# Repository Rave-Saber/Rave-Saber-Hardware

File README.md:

# RaveSaber - AVR Hardware

This repository contains the circuit diagram, PCB schematics, prototype board
layout, parts list, & setup guide for the RaveSaber electronics.

There is no blade or hilt at the moment, but you can swing the LEDs
around using the PCB or prototype board & a piece of wood.

## Electronics Design

The Rave Saber board includes voltage regulation, utility headers, input
buttons, and an Atmel ATmega168a microchip.

### Connectors

`J1` is where power enters the board from the battery. We use JST connectors
for our battery wiring. The battery power is fed through the power sub-circuit
to get a regulated voltage of 5V.

`J2` is where the Dotstar strips connect to the board. The data & clock signals
come from the microchip while the power connections come from the power
circuit.

`J3` & `J4` are optional connectors that ease programming & development. `J3`
is a FTDI Serial connection that can be used to preview/sample different colors
with our [color testing firmware][color-test]. `J4` is an ISP connector that
allows you to re-program the microchip without having to pull it out of it's
socket.

### Power

The power circuit uses a LM2576TV-5G switching voltage regulator to step down
the battery voltage to 5V. It can pump out a maximum of 3 Amps, which is used
to power the microcontroller & the LEDs.

The circuit design is derived from the voltage regulator's datasheet. `C1` &
`C2` should be low-ESR capacitors rated for at least 16V(with a minimum ESR of
50 milliOhms for `C2`). `C2` can be anywhere from 1000 to 2000 uF. `L1` must be
an inductor rated for at least 3 amps, going slightly over that is encouraged.
`D1` should be rated for 20V.

### Microcontroller

The microcontroller circuit is mostly just connections to the other circuits.

Bypass capacitors are used on the connection to the power circuit. `C3` & `C4`
are optional but `C5`, the 100nF capacitor, should always be included. The
analog reference & power pins are connected to the power supply even though
they are not used - this is recommended in the ATmega datasheet.

### Crystal Oscillator

The oscillator circuit is pretty fluid. You can use a different frequency
crystal(with a maximum of 20Mhz), or leave out the entire circuit and use the
ATmega's 8Mhz internal oscillator instead. If you do modify the circuit, make
sure your microcontroller's fuses are correctly programmed for your desired
clock source and change the definition of the `F_CPU` macro in the firmware's
`Makefile` to your new frequency.

### Button

The main button is `SW1`. It is used to ignite/extinguish the saber & cycle
through the programmed patterns. We've included both a tactile switch for
development and an external connection so you can put your board in a hilt.

The reset button, `SW2`, is optional but ocassionally useful for testing &
development.

## Required Materials

### Equipment

You'll want to have the following equipment/supplies:

* 22AWG Solid Hookup Wire
* AVR Programmer(like the [USBtinyISP][usbtinyisp])
* Wire Strippers
* Flush Cutters
* Soldering Iron & Solder
* PCB Holder(optional)
* Anti-static Bracelet or ESD-safe Tweezers(optional)

If you're only testing this out on a breadboard you can get away with just:

* Breadboard
* Wire & Strippers
* AVR Programmer
* 5V Power Supply

### Components

For the breadboard, you just need a Dotstar strip, an ATmega168a
microcontroller & a tactile button.

For the prototyping board, you will need the following:

| Part | Description | Link |
|---|---|---|
| | 22x27 through-hole prototyping board | [Amazon][protoboard] |
| BAT | 7.4v Li-Ion battery | [TCSS][battery] |
| LED | DotStar Strip, 144/m | [Mouser][led-strip] |
| J1 | 2-pin JST connector | [TCSS][jst-power-connector] |
| J2 | 4-pin, 2.54mm pitch male header | [Amazon][headers] |
| J3 | 6-pin, 2.54mm pitch male header | [Amazon][headers] |
| J4 | 2x3-pin, 2.54mm pitch male header | [Amazon][headers] |
| C1 | 100uF low-ESR electrolytic capacitor | [Mouser][100-cap] |
| C2 | 1000-2000uF low-ESR electrolytic capacitor | [Mouser][1200-cap] |
| C3 | 10uF capacitor | [Amazon(assorted)][elec-cap-kit] |
| C4 | 1uF capacitor | [Amazon(assorted)][elec-cap-kit] |
| C5 | 100nF capacitor | [Amazon(assorted)][cer-cap-kit] |
| C6, C7 | 20pF capacitor | [Mouser][20-cap] |
| D1 | 3A, 20V Schottky Diode | [Mouser][diode] |
| L1 | 47uH, 3A Fixed Inductor | [Mouser][inductor] |
| Y1 | 16Mhz Crystal | [Mouser][crystal] |
| SW1, SW2 | 6mm SPST OFF-(ON) tactile switch | [Mouser][switch] |
| U1 | LM2576TV-5G - 5V, 3A switching voltage regulator | [Mouser][vreg] |
| U2 | 28-pin DIP IC socket | [Amazon][dip-socket] |
| U2 | Atmel ATmega168A-PU - AVR microcontroller | [Mouser][atmega] |

[protoboard]: https://amzn.to/2L2IWVJ
[battery]: http://www.thecustomsabershop.com/74v-Li-ion-2600mAh-18650-Battery-Pack-P699.aspx
[led-strip]: https://www.mouser.com/ProductDetail/485-2242
[jst-power-connector]: https://www.thecustomsabershop.com/JST-Female-connector-24AWG-RedBlack-P964.aspx
[headers]: https://amzn.to/2Mx6HtK
[100-cap]: https://www.mouser.com/ProductDetail/710-870135675003
[1200-cap]: https://www.mouser.com/ProductDetail/667-EEU-FC1A122S
[elec-cap-kit]: https://amzn.to/2wb0Ekk
[cer-cap-kit]: https://amzn.to/2PiyX1K
[20-cap]: https://www.mouser.com/ProductDetail/594-S200K25SL0N63L6R
[diode]: https://www.mouser.com/ProductDetail/863-1N5820G
[inductor]: https://www.mouser.com/ProductDetail/673-PE-53112NL
[crystal]: https://www.mouser.com/ProductDetail/520-HCA1600-20X
[switch]: https://www.mouser.com/ProductDetail/506-FSM4JH
[vreg]: https://www.mouser.com/ProductDetail/863-LM2576TV-5G
[dip-socket]: https://amzn.to/2Mo4dOU
[atmega]: https://www.mouser.com/ProductDetail/556-ATMEGA168A-PU

For the circuit board, you will need SMD components instead:

| Part | Description | Link
|---|---|---|
| | RaveSaber v3.0.0 PCB | [OSHPark][pcb-3.0.0]
| BAT | 7.4v Li-Ion battery | [TCSS][battery] |
| LED | DotStar Strip, 144/m | [Mouser][led-strip] |
| J1 | 2-pin JST connector | [TCSS][jst-power-connector]
| J2 | 4-pin, 2.54mm pitch male header | [Mouser][pcb-4-pin]
| J3 | 6-pin, 2.54mm pitch male header | [Mouser][pcb-6-pin]
| J4 | 2x3-pin, 2.54mm pitch male header | [Mouser][pcb-2-3-pin]
| J5 | 2-pin JST connector | [TCSS][jst-switch-connector]
| C1 | 100uF low-ESR electrolytic capacitor | [Mouser][pcb-100-cap] |
| C2 | 1500uF low-ESR electrolytic capacitor | [Mouser][pcb-1500-cap] |
| C3 | 10uF capacitor | [Mouser][pcb-10-cap] |
| C4 | 1uF capacitor | [Mouser][pcb-1-cap] |
| C5 | 100nF capacitor | [Mouser][pcb-100n-cap] |
| C6, C7 | 20pF capacitor | [Mouser][pcb-20-cap] |
| D1 | 3A, 20V Schottky Diode | [Mouser][pcb-diode] |
| L1 | 47uH, 3A Fixed Inductor | [Mouser][pcb-inductor] |
| Y1 | 20Mhz Crystal | [Mouser][pcb-crystal] |
| SW1, SW2 | 4.5mm SPST OFF-(ON) tactile switch | [Mouser][pcb-switch] |
| U1 | LM2576TV-5G - 5V, 3A switching voltage regulator | [Mouser][vreg] |
| U2 | 28-pin DIP IC Socket | [Mouser][pcb-dip-socket] |
| U2 | Atmel ATmega168A-PU - AVR microcontroller | [Mouser][atmega] |

NOTE: The 4- & 6-pin headers link to a 20-pin header. We simply break this into
the sizes necessary with some pliers.

NOTE: The DIP socket for `U2` is machine-holed. You may prefer a leaf-spring
socket instead.

[pcb-3.0.0]: https://oshpark.com/shared_projects/t8VlH9g8
[pcb-4-pin]: https://www.mouser.com/ProductDetail/Samtec/TSM-120-01-S-SV-P
[pcb-6-pin]: https://www.mouser.com/ProductDetail/Samtec/TSM-120-01-S-SV-P
[pcb-2-3-pin]: https://www.mouser.com/ProductDetail/855-M20-8750342
[jst-switch-connector]: https://www.thecustomsabershop.com/JST-Female-connector-24AWG-BlueWhite-P958.aspx
[pcb-100-cap]: https://www.mouser.com/ProductDetail/661-EMZJ350A101MHA0G
[pcb-1500-cap]: https://www.mouser.com/ProductDetail/598-AFK158M16H32T-F
[pcb-10-cap]: https://www.mouser.com/ProductDetail/810-C1608X5R1E106M
[pcb-1-cap]: https://www.mouser.com/ProductDetail/80-C0603X105J4R
[pcb-100n-cap]: https://www.mouser.com/ProductDetail/581-0603X7R104JT1AT
[pcb-20-cap]: https://www.mouser.com/ProductDetail/603-CC603GRNPO9BN200
[pcb-diode]: https://www.mouser.com/ProductDetail/621-B320A-F
[pcb-inductor]: https://www.mouser.com/ProductDetail/710-744373965470
[pcb-crystal]: https://www.mouser.com/ProductDetail/559-FOXSDLF200-20
[pcb-switch]: https://www.mouser.com/ProductDetail/612-TL3305AF260QG
[pcb-dip-socket]: https://www.mouser.com/ProductDetail/575-1104732841105000

## Setup

### Breadboard

A breadboard can be used for simple testing of colors/patterns as well as
flashing the microchip with new firmware. You could use a smaller breadboard
for the saber instead of a prototyping board, but it's not nearly as durable.
Be wary of drawing too much current through your breadboard - you might melt
it! Initial attempts used batteries and voltage regulation with the breadboard,
but these instructions will assume you are running everything off a 5V bench
power supply.

1. Place the ATmega168a chip in the center of the breadboard.
1. Connect the switch to ground and pin 4(PD2/INT0) of the microchip.
1. Connect pin 19(SCK) to the Dotstar strip's clock pin & pin 17(MOSI) to the
   strip's data pin.
1. Connect your power supply's 5V & ground leads to the microchip & Dotstar
   strip.

You should now be able to connect the GND, SCK, MOSI, MISO, & RESET pins of
your programmer and flash your chip with the [RaveSaber Firmware][firmware].
Leave the VCC pin on your programmer unconnected since power is coming from
your bench supply.

### Prototyping Board

A prototyping board is the recommended way to setup v2.0.0 of the RaveSaber
hardware.

The prototyping board is assembled by placing components and bridging pads with
component leads, solder bridges, & wire. We've ommited `C4`, the 1uF decoupling
capacitor but feel free to add it in.

First we place the components and make what connections we can with the
component leads:

1. Start by placing the capacitors on the board and bending the leads so they
   stay on the board when you flip it over. You can also tack them into place
   with a small amount of solder.
1. Place the switches and voltage regulator. These should fit tight enough that
   they don't fall out when you flip the board over. If they do, tack them into
   place with some solder on the pins.
1. Place the DIP socket for `U2` and tack it into place by soldering some of
   the unused pins.
1. Connect `C1` and `U1` by bending the leads of `C1` and soldering them together.
1. Bridge `GND` & `ON/OFF` of `U1` together. This keeps the regulator always
   running.
1. Place and solder `L1`. Bend & solder the positive lead of `C2` to connect
   the two.
1. Since the leads of `D1` are too thick for the board's holes, bend them down
   the board and solder each one over multiple pads.
1. Connect and solder the negative leads of `C2`, `C3`, `C5`, & `SW2`. Do the
   same with the positive leads of `C3` & `C5`.
1. Use spare lead cuttings to bridge all the ground pins of `SW1` & `SW2`
   together. Bridge the top pins of each switch together as well, keeping the
   tops of `SW1` & `SW2` unconnected.
1. Place & solder `Y1`. Use the right leads of `C6` & `C7` to connect & solder
   them to the crystal and then to the proper DIP-socket pins.
1. Place and solder the `J2`, `J3`, & `J4` headers. Use just enough solder to
   get them to hold into place - it'll make their wire connections easier to
   solder.
1. Bridge the ground pins of the serial & LED headers together. Leave space for
   the ground wire between `C2` and the LED header.

Everything should now be on the board & the remaining connections can be made
with your 22-gauge wire. We did this in the following order:

1. `U1` to `L1`, `D1`, & `C2`.
1. `C3` positive lead to `C2`.
1. `C5` to VCC & GND of `U2`.
1. `U2` second GND(pin 22) to `SW1`.
1. `RESET` from `U2` to `SW2`.
1. `BTN` from `U2` to `SW1`.
1. `TXD` from `U2` to `RXD` of the serial header, followed by `RXD` to `TXD`.
1. `RESET` from `U2` to the ISP header.
1. `C2` to VCC & GND of the LED header.
1. `GND` from `C2` to `C6`, `C7`, & the ISP header.
1. `MOSI` & `SCK` from `U2` to the LED header.
1. `MOSI`, `MISO`, `SCK` from `U2` to the LED header.
1. Connect two wires to `C1` and terminate them with the JST connector.

Everything should be connected, your circuit should resemble the schematics, &
your prototyping board should resemble the above layout.

Place the ATmega168a into the DIP socket at `U2` & connect your Programmer's
ISP cable and the battery. Flash the [RaveSaber Firmware][firmware] &
disconnect the programmer & battery.

### PCB Assembly

You should be decent at soldering SMD components before attempting this.

We recommend soldering `C3` through `C7` first, followed by `U2`, `SW1`, `Y1`,
`SW2`, `J2` through `J4`, `D1`, `C1`, `L1`, `C2`, & finally `U2`. Use female
JST cables for `J1` & `J5`. Scrub with isopropyl alcohol to clean off any flux.

You can now insert & flash the microchip, plug in the battery, connect the
lights, and long-press `SW1` to extend the blade.

### Saber Blade / Hilt

The saber blade & hilt construction is very simple - we haven't put together a
blade or hilt yet so we just attach our LEDs & protoboard to a piece of wood.
We used a long 1x2 that we cut down after assembly. It's heavy, but you can
actually swing it around.

1. Lay your DotStar strip at the end of your board & secure it with 4-5
   zipties. Start at the far end, keeping the strip flat as you work towards
   the center of your wood.
1. Place the prototyping board below the strip, secure it with zipties at both
   ends and one in the center.
1. Flip the board over and place your battery near the board & strip, secure it
   with 3 zipties.
1. Connect the LED strip to the 4-pin header on the board and connect your
   battery to the board's JST connector.

You should now be able to long-press the button to illumunate the blade then
short-press to switch patterns or long-press again to power down the blade.

## TODO

* Auto-generate BOM(using [KiBoM](https://github.com/SchrodingersGat/KiBoM)?)
    * Make sure to add DIP socket, LED strips, etc. to BoM
* Blade construction guide, using TCSS blade parts
* PVC Hilt construction guide
    * Eventually use MHS hilts as well, but that's not open hardware
    * See how much it'd cost to get someone to design an open/free metal hilt
      that machinists could reproduce.
    * Chassis disk design, for use w/ acrylic laser cutting service or online
      machine shop.
* Contact Saber design
    * For doing moves [like this](https://youtu.be/Wgl2wym96k0)
    * Needs to be well balanced - some kind of chassis weighting?
    * Research best balance point for contact sabering
* Recharge port? Recharging blade stub?

### Future Milestones

Rough drafts of future plans

* v3.1.0 - 90deg ISP pins? Source single component for all 1-row pins & have
  assembler break apart. blade build + guide
* v4.0.0 - pcb & chassis that fits in MHS hilts

## References

### Hilts

* [Jay-gon's PVC Hilt Tutorial](http://forums.thecustomsabershop.com/showthread.php?3266-Jay-gon-s-PVC-Hilts-Full-tutorial-on-last-page&p=138540&viewfull=1#post138540)

### Blades

* [Neopixel Blade Assembly - FX-Sabers](https://www.fx-sabers.com/forum/index.php?PHPSESSID=06jl1sddsstpq4hvnu0c9fat74&topic=51357.0)
* [LED Blade Assembly](https://www.youtube.com/watch?v=Qbl4K-v4G_s)

## License

CERN OHL v1.2

[color-test]: https://github.com/Rave-Saber/AVR-APA102-Color-Tester
[usbtinyisp]: https://learn.adafruit.com/usbtinyisp/overview
[mouser]: https://mouser.com
[firmware]: https://github.com/Rave-Saber/Rave-Saber-Firmware

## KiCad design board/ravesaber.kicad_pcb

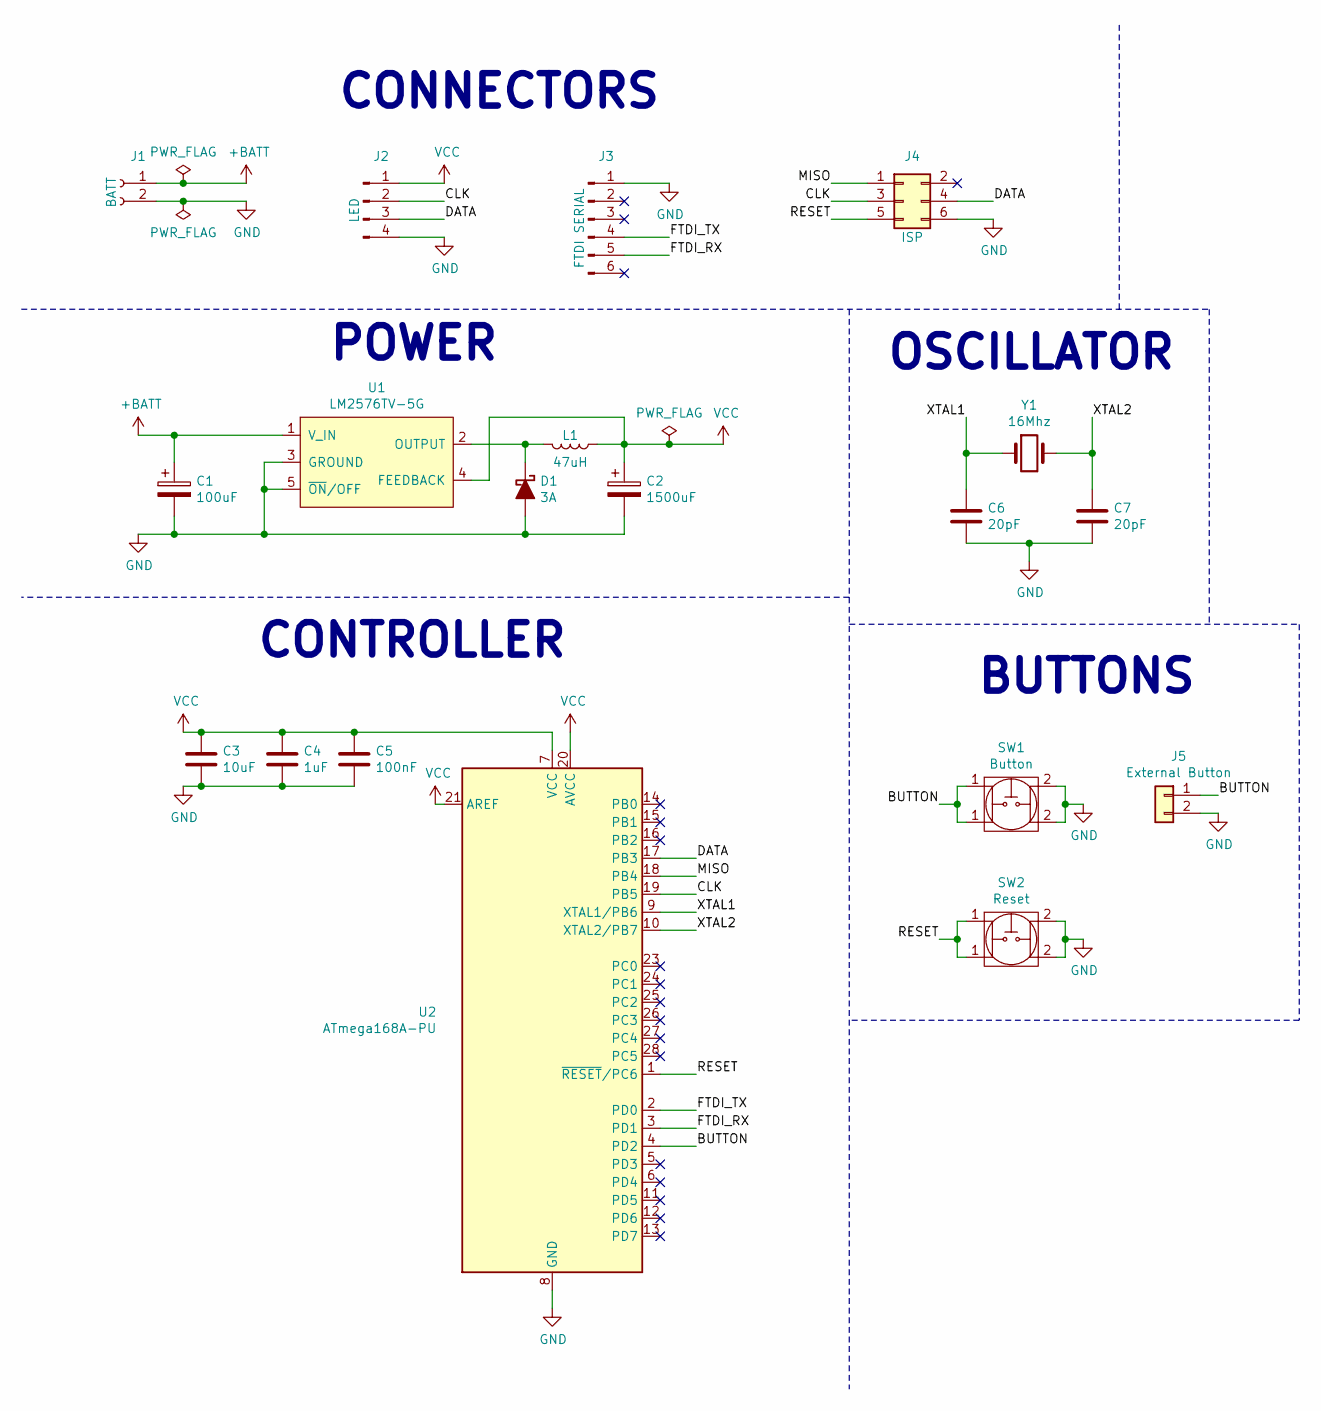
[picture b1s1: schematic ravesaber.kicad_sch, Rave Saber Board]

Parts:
C1: 100uF; CP_Elec_8x10; Mouser # 661-EMZJ350A101MHA0G
C2: 1500uF; CP_Elec_16x17.5; Mouser # 598-AFK158M16H32T-F
C3: 10uF; C_0603_1608Metric_Pad1.05x0.95mm_HandSolder; Mouser # 810-C1608X5R1E106M
C4: 1uF; C_0603_1608Metric_Pad1.05x0.95mm_HandSolder; Mouser # 80-C0603X105J4R
C5: 100nF; C_0603_1608Metric_Pad1.05x0.95mm_HandSolder; Mouser # 581-0603X7R104JT1AT
C6, C7: 20pF; C_0603_1608Metric_Pad1.05x0.95mm_HandSolder; Mouser # 603-CC603GRNPO9BN200
D1: 3A; D_SMA_Handsoldering; Mouser # 621-B320A-F
J1: BATT; SolderWirePad_1x02_P3.81mm_Drill1.2mm
J2: LED; PinHeader_1x04_P2.54mm_Vertical_SMD_Pin1Left; Mouser # 437-3508010400106101
J3: FTDI SERIAL; PinHeader_1x06_P2.54mm_Vertical_SMD_Pin1Left; Mouser # 855-M20-8770642R
J4: ISP; PinHeader_2x03_P2.54mm_Vertical_SMD; Mouser # 855-M20-8750342
J5: External Button; SolderWirePad_1x02_P3.81mm_Drill1.2mm
L1: 47uH; Wuerth WE-LHMI SMD; Mouser # 710-744373965470
SW1: Button; SW_SPST_TL3305A; Mouser # 612-TL3305AF260QG
SW2: Reset; SW_SPST_TL3305A; Mouser # 612-TL3305AF260QG
U1: LM2576TV-5G; TO-220-5_P3.4x3.7mm_StaggerOdd_Lead3.8mm_Vertical; Mouser # 863-LM2576TV-5G
U2: ATmega168A-PU; DIP-28_W8.89mm_SMDSocket_LongPads; Mouser # 556-ATMEGA168A-PU
Y1: 16Mhz; Crystal_SMD_HC49-SD; Mouser # 559-FOXSD160-20-LF

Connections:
+BATT: C1.1, J1.1, U1.1 (V_IN)
/BUTTON: J5.1, SW1.1, U2.4 (PD2)
/CLK: J2.2, J4.3, U2.19 (PB5)
/DATA: J2.3, J4.4, U2.17 (PB3)
/FTDI_RX: J3.5, U2.3 (PD1)
/FTDI_TX: J3.4, U2.2 (PD0)
/MISO: J4.1, U2.18 (PB4)
/RESET: J4.5, SW2.1, U2.1 (~RESET~/PC6)
/XTAL1: C6.1, U2.9 (XTAL1/PB6), Y1.1
/XTAL2: C7.1, U2.10 (XTAL2/PB7), Y1.2
GND: C1.2, C2.2, C3.2, C4.2, C5.2, C6.2, C7.2, D1.2 (A), J1.2, J2.4, J3.1, J4.6, J5.2, SW1.2, SW2.2, U1.3 (GROUND), U1.5 (~ON~/OFF), U2.8 (GND), U2.22 (GND)
unnamed: D1.1 (K), L1.2, U1.2 (OUTPUT)
VCC: C2.1, C3.1, C4.1, C5.1, J2.1, L1.1, U1.4 (FEEDBACK), U2.7 (VCC), U2.20 (AVCC), U2.21 (AREF)

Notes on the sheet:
CONTROLLER
POWER
CONNECTORS
OSCILLATOR
BUTTONS

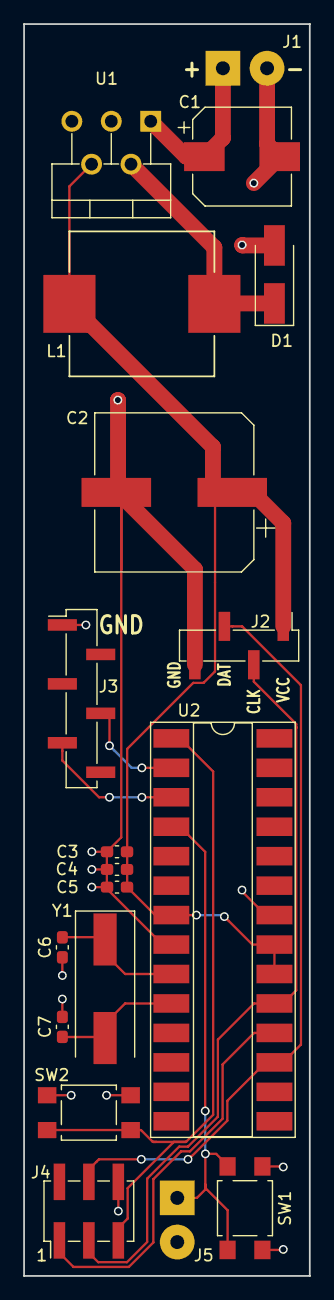
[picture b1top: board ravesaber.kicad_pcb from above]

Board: 2 copper layers, 24.6 x 108.0 mm, 20 parts (1 on the bottom side), 13 nets.

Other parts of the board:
svg2mod: G***; AntiFA_Logo

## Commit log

2018-07-03 Add README & LICENSE Files
2018-07-03 Add Parts/Setup Info, Schematics, BOM, & Breadboard Drawing
2018-07-03 Add CHANGELOG
2018-07-03 Fix Image URLs
2018-08-13 Use KiCAD to Create Schematic
    This adds a new KiCAD v5 project to the repository, containing a new
    board schematic with a custom symbol for the voltage regulator, as well
    a footprint for our eventual SMD inductor.
    The new schematic includes a voltage regulation circuit for running off
    of battery power, a reset button, a crystal oscillator circuit,
    decoupling capacitors on the chip's power pins & ISP/FTDI headers.
2018-08-13 Add Design & Prototyping Board Documentation
    Add some documentation about the current electronic circuit's design, as
    well as a prototyping board layout with a materials/equipment list &
    setup guide.
2018-08-13 Remove the Fritzing Files
2018-08-13 Update the CHANGELOG
2018-08-13 Fix Link to Button Schematics Image
2018-08-13 Fix RX/TX Connections in Prototyping Board Layout
2018-08-15 Fix Milestones, Optimize Images
2018-08-18 Add Links to Purchase Parts to README
2018-08-18 Cleanup README, Add Links to Blade Construction Guides
2018-08-18 Document Wooden Blade/Hilt Construction
2018-08-20 Update TODOs
2018-08-20 Prepare for v2.0.0
2021-05-04 Add a KiCAD PCB Schematic With SMD Components
    Add a 1" PCB & migrate to SMD components. We've bumped C2 to 1500 uF &
    the crystal oscillator to 20Mhz. Blank through-holes have been added for
    battery & switch cables.
    This PCB has been printed by OSHPark & tested by us.
2021-05-04 Update README With PCB Documentation
2021-05-04 Link to JST Cables Instead of Connectors
2021-05-05 Prepare for v3.0.0
2021-05-06 Fix Footprint Size for C2, Fix Silkscreen for L1
    Create a new CP_Elec footprint using the datasheet for C2, swapping out
    the footprint in the PCB schematic.
    Fix the Silkscreen layer for the L1 footprint, ensuring it does not
    cross the pads.
    Shift the SW2 footprint up so that it's courtyard does not overlap the
    courtyard of J4.
2021-05-06 Change 0603 Capacitors to New Footprint
    Switch the PCB footprints for the 0603 SMD Capacitors to the new
    1.08x0.95mm hand-soldering version from KiCad 5.99.
2021-05-06 Refill All PCB Ground Plane Zones
2021-05-06 Move Jumper & Switch Labels Outside of Their Footprints
2021-05-06 Update CHANGELOG
2021-05-06 Fix Component Links for J2 & J3; Add Note That U2 is Machine-Holed
2021-05-15 README Cleanup

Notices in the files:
board/ravesaber.kicad_pcb:
GPL v3.0
